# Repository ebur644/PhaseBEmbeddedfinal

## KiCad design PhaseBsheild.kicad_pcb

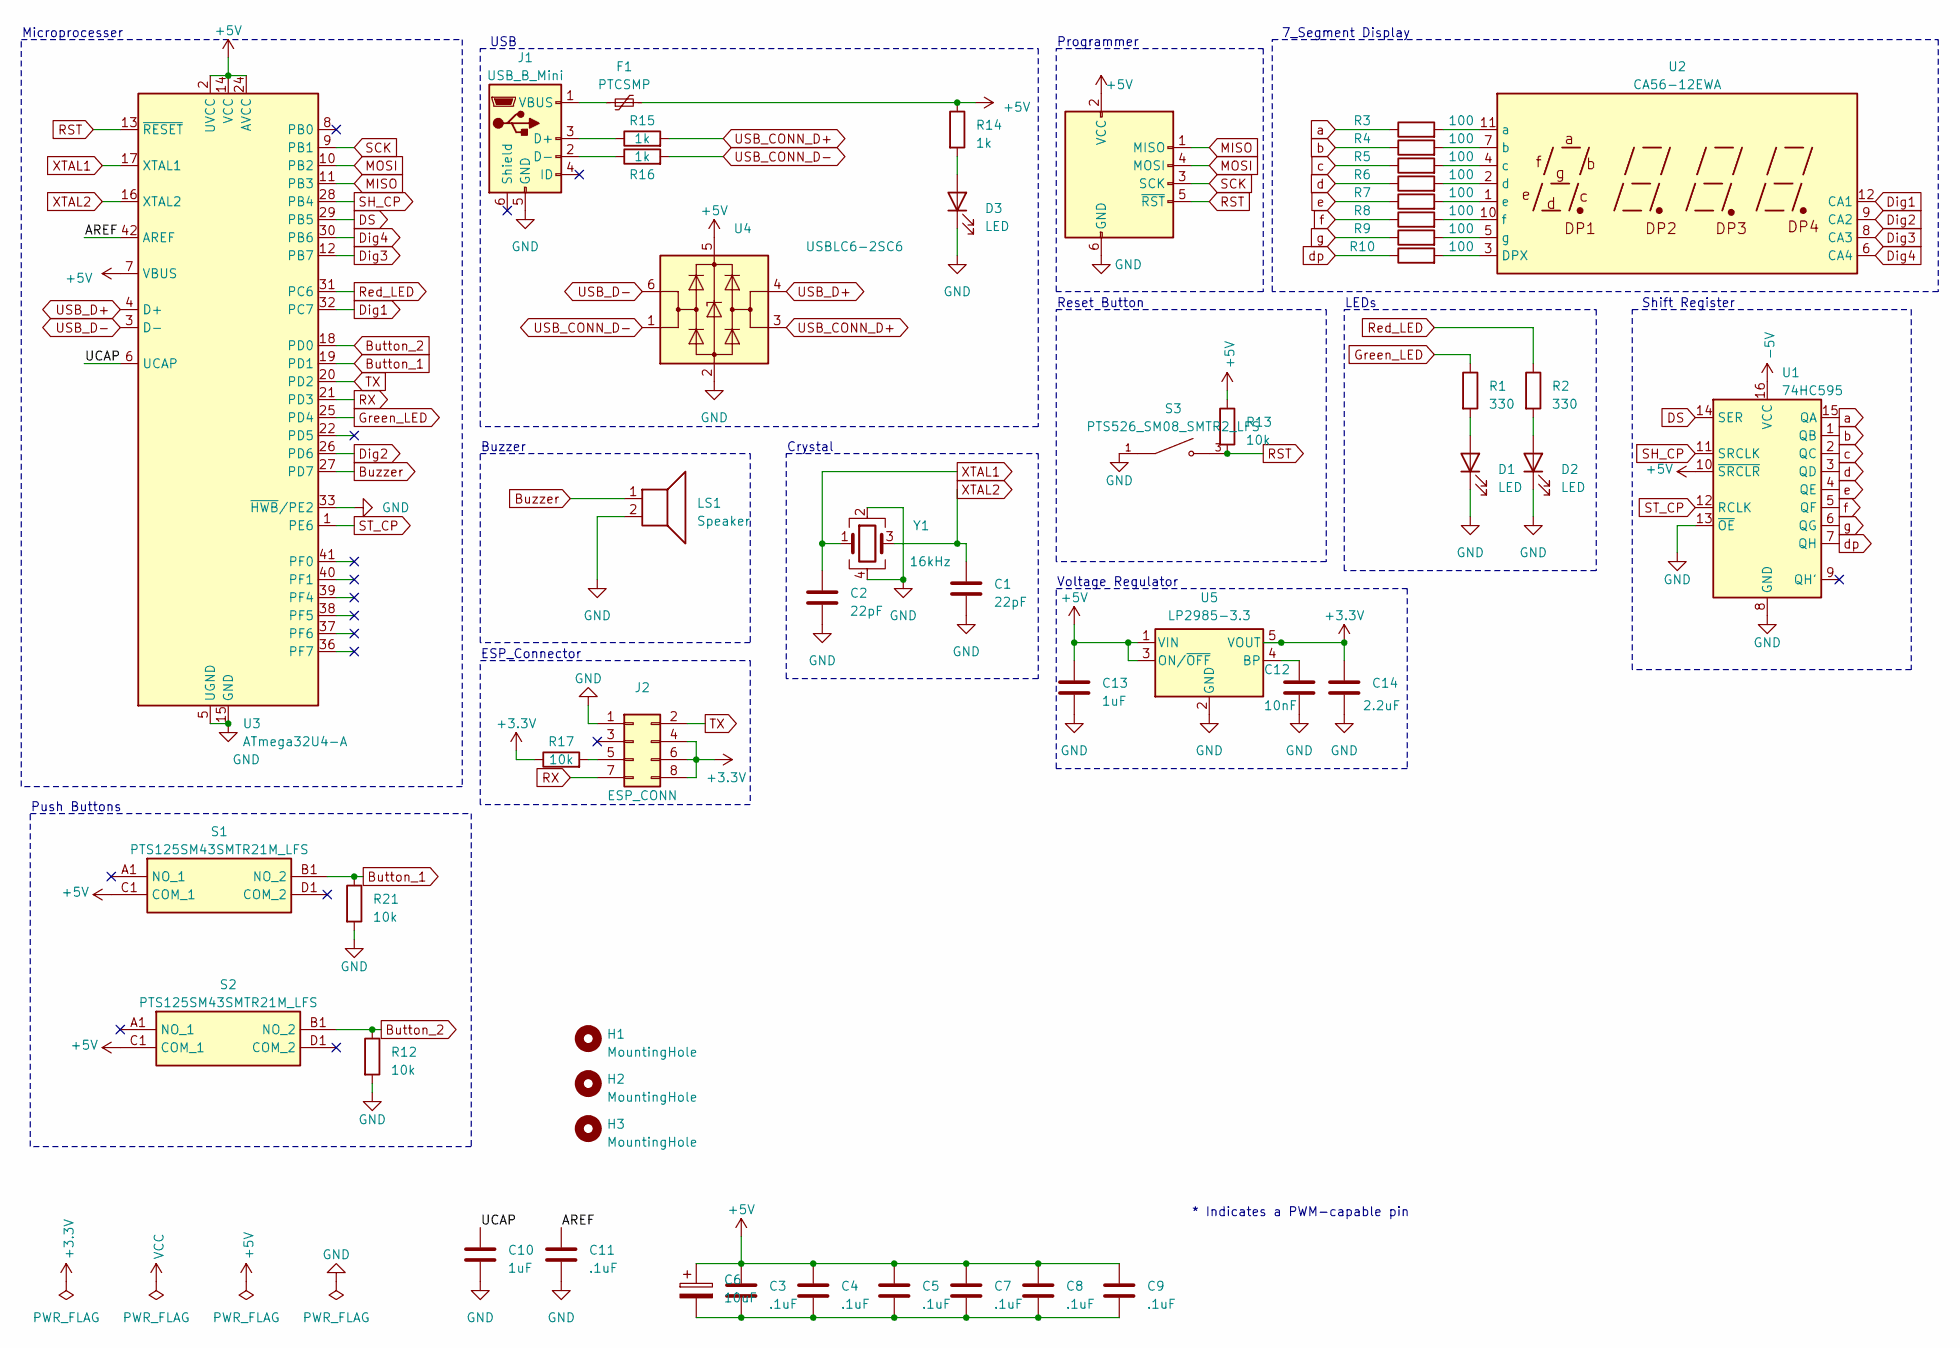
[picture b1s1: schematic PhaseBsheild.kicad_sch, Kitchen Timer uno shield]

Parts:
C1, C2: 22pF; C_0603_1608Metric
C3, C4, C5, C7, C8, C9, C11: .1uF; C_0603_1608Metric
C6: 10uF; C_0805_2012Metric
C10, C13: 1uF; C_0603_1608Metric
C12: 10nF; C_0603_1608Metric
C14: 2.2uF; C_0603_1608Metric
D1, D2, D3: LED; LED_0805_2012Metric
F1: PTCSMP; Fuse_1812_4532Metric
H1, H2, H3: MountingHole; MountingHole_3mm
J1: USB_B_Mini; USB_Mini-B_Lumberg_2486_01_Horizontal
J2: ESP_CONN; PinSocket_2x04_P2.54mm_Vertical
J3: AVR-ISP-6; PinSocket_2x03_P2.54mm_Vertical
LS1: Speaker; Buzzer_12x9.5RM7.6
R1, R2: 330; R_0805_2012Metric
R3, R4, R5, R6, R7, R8, R9, R10: 100; R_0805_2012Metric
R12, R13, R17, R21: 10k; R_0603_1608Metric
R14: 1k; R_0805_2012Metric
R15, R16: 1k; R_0603_1608Metric
S1, S2: PTS125SM43SMTR21M_LFS; PTS125_SMD_Button; Manufacturer_Part_Number PTS125SM43SMTR21M LFS; Mouser Part Number 611-PTS125S43SMTRLFS
S3: PTS526_SM08_SMTR2_LFS; PTS526_SMD_Button; PARTREV 20 mar 19
U1: 74HC595; TSSOP-16_4.4x5mm_P0.65mm
U2: CA56-12EWA
U3: ATmega32U4-A; TQFP-44_10x10mm_P0.8mm
U4: USBLC6-2SC6; SOT-23-6
U5: LP2985-3.3; SOT-23-5
Y1: 16kHz; Crystal_SMD_Abracon_ABM8G-4Pin_3.2x2.5mm

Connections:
+3.3V: C14.1, J2.4, J2.6, J2.8, R17.1, U5.5 (VOUT)
/AREF: C11.1, U3.42 (AREF)
/UCAP: C10.1, U3.6 (UCAP)
Button_1: R21.1, S1.B1 (NO_2), U3.19 (PD1); also elsewhere on the board
Button_2: R12.1, S2.B1 (NO_2), U3.18 (PD0); also elsewhere on the board
Buzzer: LS1.1, U3.27 (PD7)
DS: U1.14 (SER), U3.29 (PB5)
Dig1: U2.12 (CA1), U3.32 (PC7)
Dig2: U2.9 (CA2), U3.26 (PD6)
Dig3: U2.8 (CA3), U3.12 (PB7)
Dig4: U2.6 (CA4), U3.30 (PB6)
GND: C1.2, C2.2, C10.2, C11.2, C12.2, C13.2, C14.2, D1.1 (K), D2.1 (K), D3.1 (K), J1.5 (GND), J2.1, J3.6 (GND), LS1.2, R12.2, R21.2, S3.1, U1.8 (GND), U1.13 (~OE), U3.5 (UGND), U3.15 (GND), U3.23 (GND), U3.33 (~HWB/PE2), U3.35 (GND), U3.43 (GND), U4.2 (GND), U5.2 (GND), Y1.2, Y1.4; also elsewhere on the board
Green_LED: R1.1, U3.25 (PD4)
MISO: J3.1 (MISO), U3.11 (PB3)
MOSI: J3.4 (MOSI), U3.10 (PB2)
unnamed: C3.2, C4.2, C5.2, C6.2, C7.2, C8.2, C9.2
unnamed: D1.2 (A), R1.2
unnamed: D2.2 (A), R2.2
unnamed: D3.2 (A), R14.2
unnamed: J1.3 (D+), R15.1
unnamed: J1.2 (D-), R16.1
unnamed: F1.1, J1.1 (VBUS)
unnamed: J2.5, R17.2
unnamed: R10.2, U2.3 (DPX)
unnamed: R3.2, U2.11 (a)
unnamed: R4.2, U2.7 (b)
unnamed: R5.2, U2.4 (c)
unnamed: R6.2, U2.2 (d)
unnamed: R7.2, U2.1 (e)
unnamed: R8.2, U2.10 (f)
unnamed: R9.2, U2.5 (g)
unnamed: C12.1, U5.4 (BP)
RST: J3.5 (~RST), R13.2, S3.3, U3.13 (~RESET)
RX: J2.7, U3.21 (PD3)
Red_LED: R2.1, U3.31 (PC6)
SCK: J3.3 (SCK), U3.9 (PB1)
SH_CP: U1.11 (SRCLK), U3.28 (PB4)
ST_CP: U1.12 (RCLK), U3.1 (PE6)
TX: J2.2, U3.20 (PD2)
USB_CONN_D+: R15.2, U4.3 (I/O2)
USB_CONN_D-: R16.2, U4.1 (I/O1)
USB_D+: U3.4 (D+), U4.4 (I/O2)
USB_D-: U3.3 (D-), U4.6 (I/O1)
XTAL1: C2.1, U3.17 (XTAL1), Y1.1
XTAL2: C1.1, U3.16 (XTAL2), Y1.3
a: R3.1, U1.15 (QA)
b: R4.1, U1.1 (QB)
c: R5.1, U1.2 (QC)
d: R6.1, U1.3 (QD)
dp: R10.1, U1.7 (QH)
e: R7.1, U1.4 (QE)
f: R8.1, U1.5 (QF)
g: R9.1, U1.6 (QG)

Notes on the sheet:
Shift Register
Crystal
Reset Button
ESP_Connector
Push Buttons
USB
Microprocesser
Voltage Regulator
Buzzer
7_Segment Display
Programmer
* Indicates a PWM-capable pin
LEDs

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
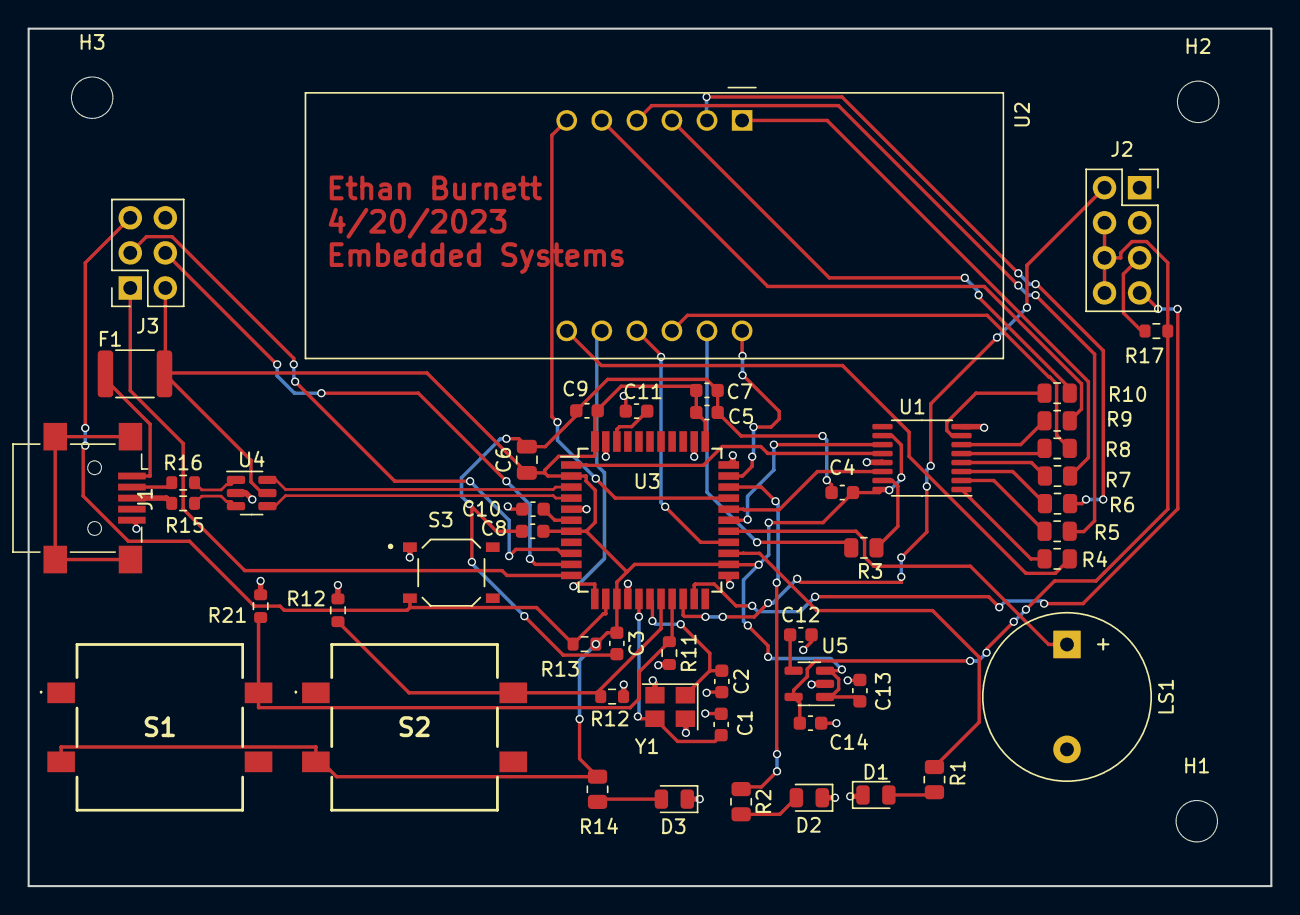
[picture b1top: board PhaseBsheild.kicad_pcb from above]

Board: 2 copper layers, 90.0 x 62.1 mm, 53 parts (0 on the bottom side), 54 nets.

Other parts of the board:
R11, R12#2: 10k; R_0603_1608Metric

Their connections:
Button_1: R11.1; also elsewhere on the board
Button_2: R12#2.1; also elsewhere on the board
GND: R11.2, R12#2.2; also elsewhere on the board

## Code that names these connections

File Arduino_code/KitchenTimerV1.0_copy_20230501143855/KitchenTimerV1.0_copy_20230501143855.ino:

#define BUTTON_1 2
#define BUTTON_2 3
#define GREEN_LED 4
#define RED_LED 5

#define DATA 9   //74HC595  pin 8 DS
#define LATCH 8  //74HC595  pin 9 STCP
#define CLOCK 7  //74HC595  pin 10 SHCP
#define BUZZER 6

#define DIGIT_4 10
#define DIGIT_3 11
#define DIGIT_2 12
#define DIGIT_1 13

unsigned char table[] = { 0x3f, 0x06, 0x5b, 0x4f, 0x66, 0x6d, 0x7d, 0x07, 0x7f, 0x6f, 0x77, 0x7c, 0x39, 0x5e, 0x79, 0x71, 0x00 };

unsigned char setnum = 90;
unsigned char count = setnum;

unsigned int lastButtonState = 0;     // variable for reading the pushbutton status
unsigned int currentButtonState = 0;  // variable for reading the pushbutton status
unsigned int buttonState = 0;         // variable for reading the pushbutton status

volatile unsigned char isr_1_flag = 0;
volatile unsigned char isr_2_flag = 0;
volatile unsigned char isr_3_flag = 0;

volatile bool pause = 0;

void setup() {

  // LEDs Pins
  pinMode(RED_LED, OUTPUT);
  pinMode(GREEN_LED, OUTPUT);

  // Button Pins
  pinMode(BUTTON_1, INPUT_PULLUP);
  attachInterrupt(digitalPinToInterrupt(BUTTON_1), Button_1_ISR, CHANGE);
  pinMode(BUTTON_2, INPUT_PULLUP);
  attachInterrupt(digitalPinToInterrupt(BUTTON_2), Button_2_ISR, CHANGE);

  // 7-Seg Display
  pinMode(DIGIT_1, OUTPUT);
  pinMode(DIGIT_2, OUTPUT);
  pinMode(DIGIT_3, OUTPUT);
  pinMode(DIGIT_4, OUTPUT);

  // Shift Register Pins
  pinMode(LATCH, OUTPUT);
  pinMode(CLOCK, OUTPUT);
  pinMode(DATA, OUTPUT);

  //disp_on();

  // initialize timer1
  noInterrupts();  // disable all interrupts
  TCCR1A = 0;
  TCCR1B = 0;
  TCNT1 = 0;
  OCR1A = 62500;            // compare match register 16MHz/256
  TCCR1B |= (1 << WGM12);   // CTC mode
  TCCR1B |= (1 << CS12);    // 256 prescaler
  TIMSK1 |= (1 << OCIE1A);  // enable timer compare interrupt
  interrupts();             // enable all interrupts
}

void Display1(unsigned char num) {
  disp_off();
  digitalWrite(DIGIT_4, LOW);
  digitalWrite(LATCH, LOW);
  shiftOut(DATA, CLOCK, MSBFIRST, table[num]);
  digitalWrite(LATCH, HIGH);
}
void Display2(unsigned char num) {
  disp_off();
  digitalWrite(DIGIT_3, LOW);
  digitalWrite(LATCH, LOW);
  shiftOut(DATA, CLOCK, MSBFIRST, table[num]);
  digitalWrite(LATCH, HIGH);
}
void Display3(unsigned char num) {
  disp_off();
  digitalWrite(DIGIT_2, LOW);
  digitalWrite(LATCH, LOW);
  shiftOut(DATA, CLOCK, MSBFIRST, table[num]);
  digitalWrite(LATCH, HIGH);
}
void Display4(unsigned char num) {
  disp_off();
  digitalWrite(DIGIT_1, LOW);
  digitalWrite(LATCH, LOW);
  shiftOut(DATA, CLOCK, MSBFIRST, table[num]);
  digitalWrite(LATCH, HIGH);
}

void Display_Numbers() {
  Display1(count % 10);
  delay(5);
  Display2(count / 10 % 6);
  delay(5);
  Display3(count / 60 % 10);
  delay(5);
  Display4(count / 600 % 10);
  delay(5);
}


void disp_on() {
  digitalWrite(DIGIT_1, LOW);
  digitalWrite(DIGIT_2, LOW);
  digitalWrite(DIGIT_3, LOW);
  digitalWrite(DIGIT_4, LOW);
}
void disp_off() {
  digitalWrite(DIGIT_1, HIGH);
  digitalWrite(DIGIT_2, HIGH);
  digitalWrite(DIGIT_3, HIGH);
  digitalWrite(DIGIT_4, HIGH);
}

void Button_1_ISR() {
  // Set ISR Flag
  isr_1_flag = 1;
}

void Button_2_ISR() {
  // Set ISR Flag
  isr_2_flag = 1;
}



ISR(TIMER1_COMPA_vect)  // timer compare interrupt service routine
{
  // Set ISR Flag
  isr_3_flag = 1;
}

void activeBuzzer() {
  unsigned char i;
  unsigned char sleepTime = 1;  // ms

  for (i = 0; i < 100; i++) {
    digitalWrite(BUZZER, HIGH);
    delay(sleepTime);  //wait for 1ms
    digitalWrite(BUZZER, LOW);
    delay(sleepTime);  //wait for 1ms
  }
}

void loop() {
  Display_Numbers();
  // Combination of Pooling and Interrupt
  lastButtonState = currentButtonState;        // save the last state
  currentButtonState = digitalRead(BUTTON_2);  // read new state

  if (lastButtonState == HIGH && currentButtonState == LOW) {
    if (pause == 0) {
      pause = 1;
      digitalWrite(GREEN_LED, LOW);
      TCCR1B |= (1 << CS12);  // 256 prescaler
      TIMSK1 |= (1 << OCIE1A);
    } else {
      pause = 0;
      digitalWrite(GREEN_LED, HIGH);
      TCCR1B &= 0b11111000;  // stop clock
      TIMSK1 = 0;            // cancel clock timer interrupt
    }
  }


  if (pause == 1) {
    // Attend Button 1
    if (isr_1_flag == 1) {
      // Reset ISR Flag
      isr_1_flag = 0;

      // Code
      buttonState = digitalRead(BUTTON_1);
      digitalWrite(RED_LED, buttonState);
      count++;
    }

    // Attend Button 2
    if (isr_2_flag == 1) {
      // Reset ISR Flag
      isr_2_flag = 0;
    }

    // Attend 7-Seg Display
    if (isr_3_flag == 1 & count != 0) {
      // Reset ISR Flag
      isr_3_flag = 0;

      // Code
      count--;
    }
    if (count == 0) {
      // Reset ISR Flag
      activeBuzzer();
      //count = setnum;
    }
  }
  if(pause == 0 && count == 0){
    count = setnum;
  }
}

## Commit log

2023-05-01 Files
2023-05-03 added project files
2023-05-04 enclosure changes
2023-05-05 added report
